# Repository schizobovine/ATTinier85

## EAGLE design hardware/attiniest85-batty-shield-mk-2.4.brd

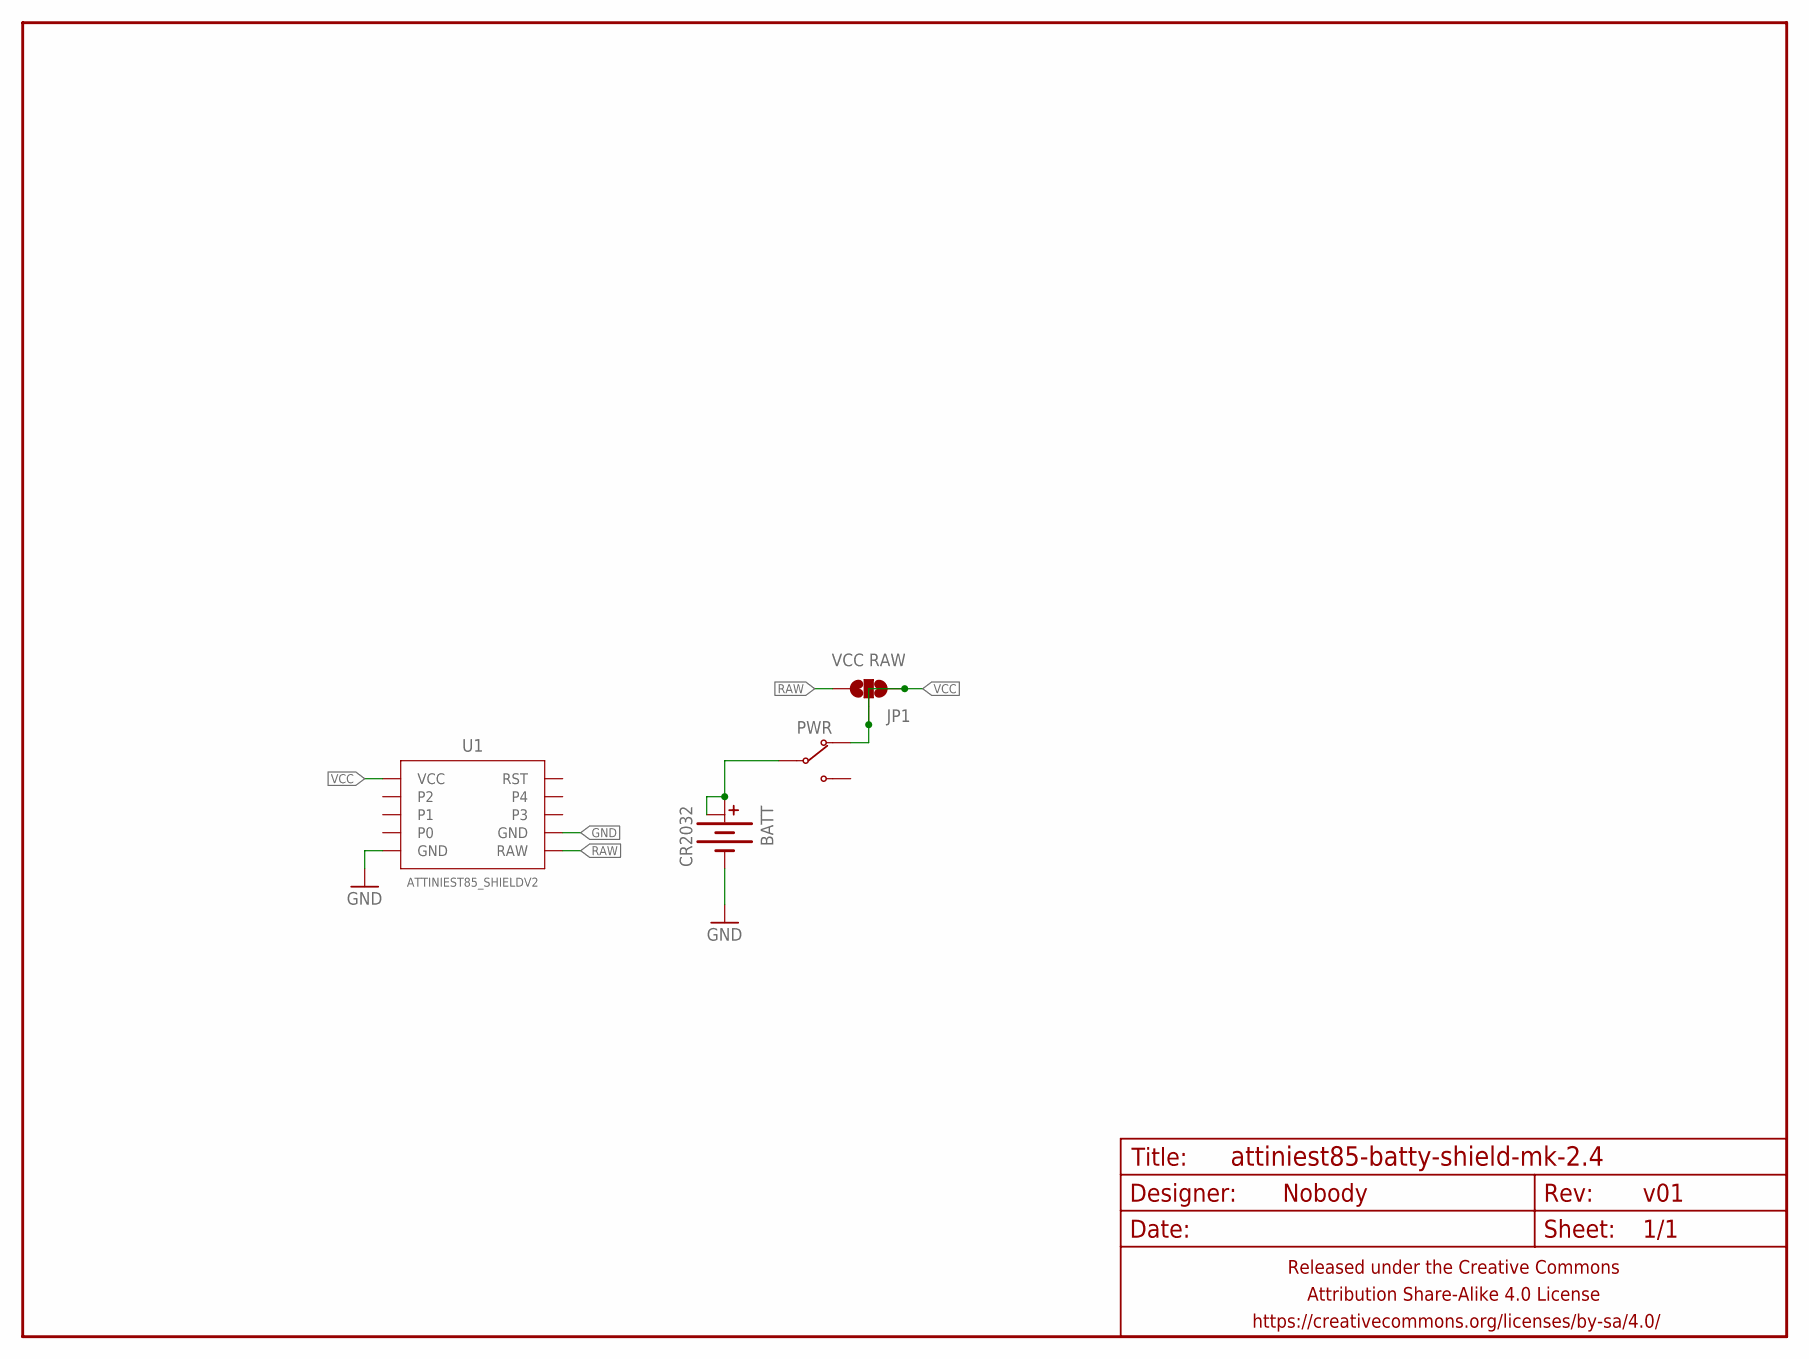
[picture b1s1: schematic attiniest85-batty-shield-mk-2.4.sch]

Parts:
BATT: CR2032; BATTCON_20MM_MINE
FRAME1: FRAME-LETTERNO_PACKAGE; DUMMY
JP1: VCC RAW; PAD-JUMPER-3-NO_YES_SILK_FULL_BOX
PWR: SWITCH-SPDTPTH-RA-2MM; SPDT-RA-2MM
U1: ATTINIEST85_SHIELDV2; ATTINIEST85_SHIELD_V2

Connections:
GND: BATT.BOTTOM (-), U1.GND@1 (GND), U1.GND@2 (GND)
RAW: JP1.1, U1.RAW
VBATT: BATT.TOP@1 (+), BATT.TOP@2 (+1), PWR.2 (COM)
VCC: JP1.2, JP1.3, PWR.1 (NC), U1.VCC

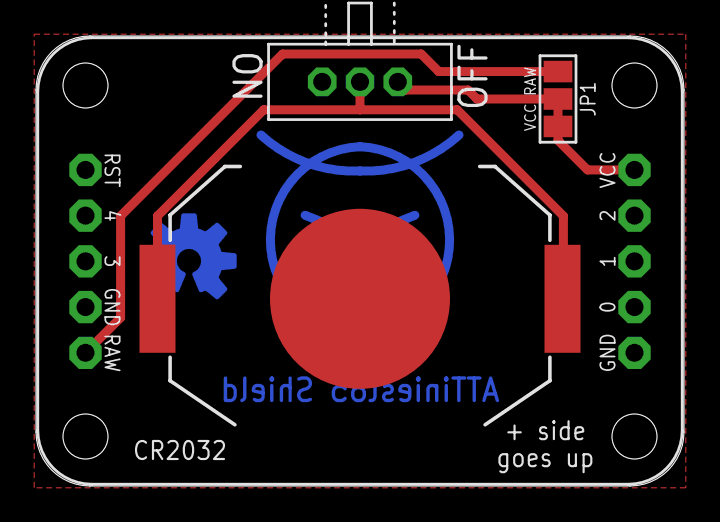
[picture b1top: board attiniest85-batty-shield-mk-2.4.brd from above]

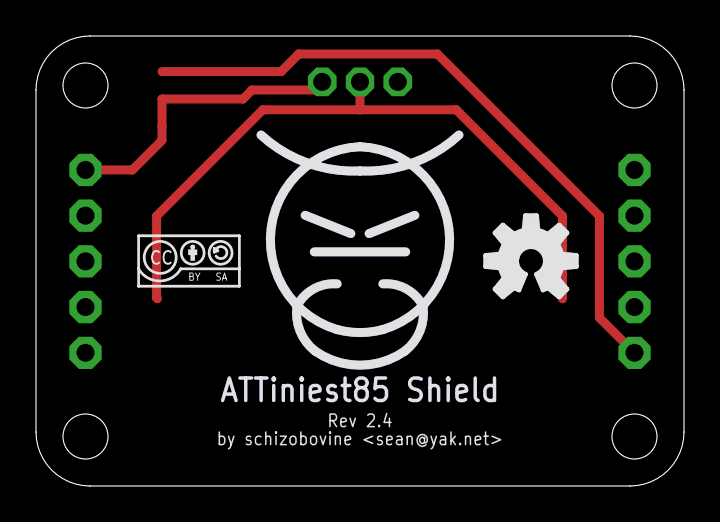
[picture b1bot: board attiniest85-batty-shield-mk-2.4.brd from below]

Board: 2 copper layers, 36.0 x 25.0 mm, 8 parts (3 on the bottom side), 4 nets.

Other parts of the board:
U$3: CC-BY-SA-4.0-NO-URL
U$4: OSHWLOGO_TOP_0.2
U$6: COW_METAL

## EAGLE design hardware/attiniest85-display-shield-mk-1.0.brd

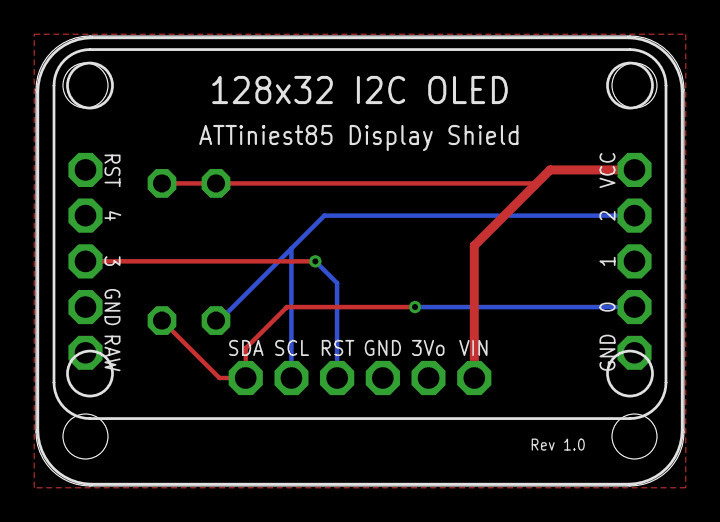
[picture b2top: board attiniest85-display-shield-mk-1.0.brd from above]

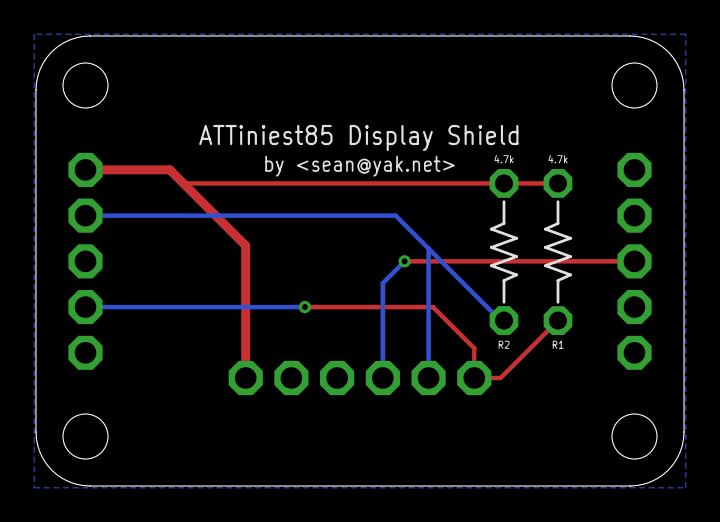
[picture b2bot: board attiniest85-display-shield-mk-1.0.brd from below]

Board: 2 copper layers, 36.0 x 25.0 mm, 5 parts (2 on the bottom side), 5 nets.

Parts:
DISPLAY1: Adafruit 128x32 OLED; ADAFRUIT_128X32_OLED_I2C_CLOSER_NOHOLES
FRAME1: DUMMY
R1, R2: 4.7k; RESISTOR-AXIAL-PTH-7.62MM
U1: ATTINIEST85_SHIELDV2; ATTINIEST85_SHIELD_V2

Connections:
DISP_RST: DISPLAY1.RST, U1.3
GND: DISPLAY1.GND, U1.GND@1, U1.GND@2
SCL: DISPLAY1.SCL, R2.P$1, U1.2
SDA: DISPLAY1.SDA, R1.P$1, U1.0
VCC: DISPLAY1.VIN, R1.P$2, R2.P$2, U1.VCC

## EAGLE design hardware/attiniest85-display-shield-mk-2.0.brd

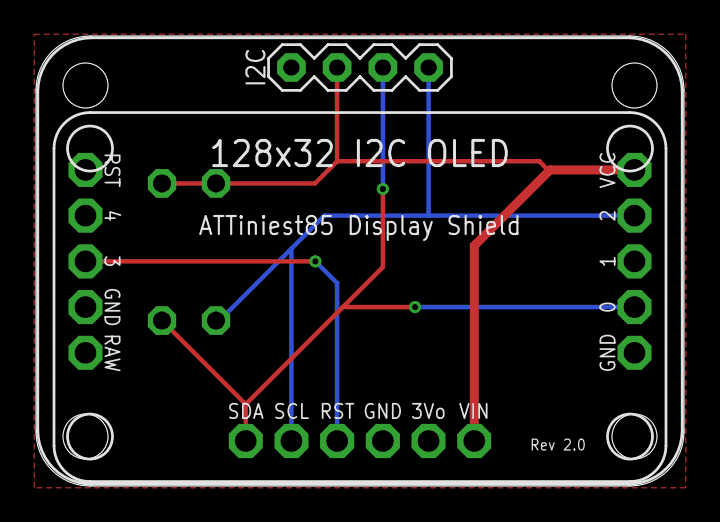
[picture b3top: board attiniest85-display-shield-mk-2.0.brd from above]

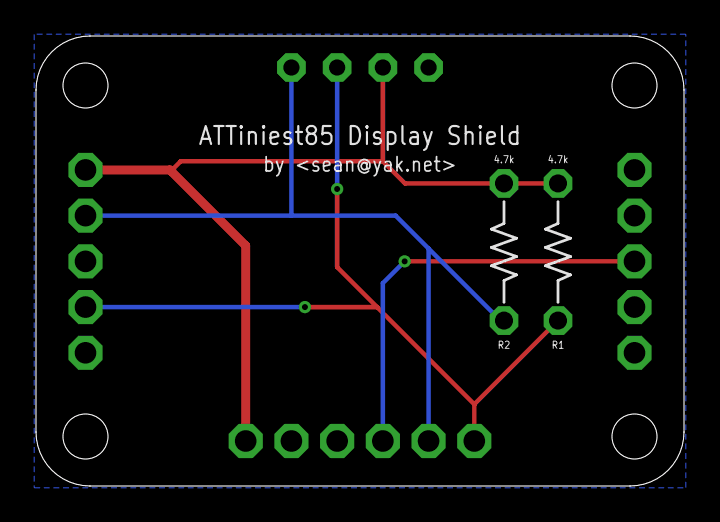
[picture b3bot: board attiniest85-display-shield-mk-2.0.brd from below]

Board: 2 copper layers, 36.0 x 25.0 mm, 6 parts (2 on the bottom side), 5 nets.

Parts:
DISPLAY1: Adafruit 128x32 OLED; ADAFRUIT_128X32_OLED_I2C_CLOSER_NOHOLES
FRAME1: DUMMY
I2C: M04PTH; 1X04-PTH-VERT
R1, R2: 4.7k; RESISTOR-AXIAL-PTH-7.62MM
U1: ATTINIEST85_SHIELDV2; ATTINIEST85_SHIELD_V2

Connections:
DISP_RST: DISPLAY1.RST, U1.3
GND: DISPLAY1.GND, I2C.1, U1.GND@1, U1.GND@2
SCL: DISPLAY1.SCL, I2C.4, R2.P$1, U1.2
SDA: DISPLAY1.SDA, I2C.3, R1.P$1, U1.0
VCC: DISPLAY1.VIN, I2C.2, R1.P$2, R2.P$2, U1.VCC

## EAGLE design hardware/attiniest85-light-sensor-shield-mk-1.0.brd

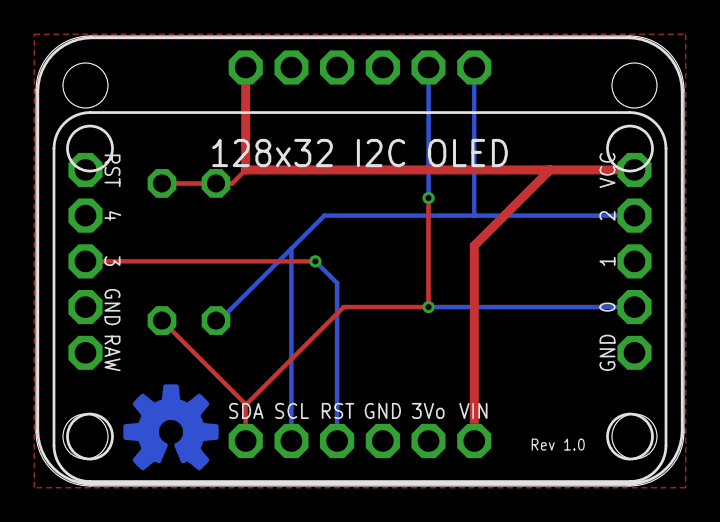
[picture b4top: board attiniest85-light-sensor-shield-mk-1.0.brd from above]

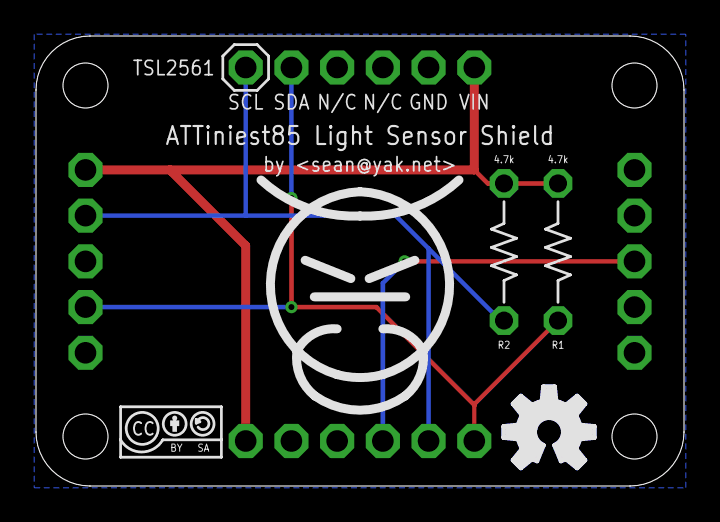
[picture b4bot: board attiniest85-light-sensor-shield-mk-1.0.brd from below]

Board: 2 copper layers, 36.0 x 25.0 mm, 9 parts (6 on the bottom side), 5 nets.

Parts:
DISPLAY1: Adafruit 128x32 OLED; ADAFRUIT_128X32_OLED_I2C_CLOSER_NOHOLES
FRAME1: DUMMY
R1, R2: 4.7k; RESISTOR-AXIAL-PTH-7.62MM
TSL2561: M06CLOSER; 1X06_CLOSER
U1: ATTINIEST85_SHIELDV2; ATTINIEST85_SHIELD_V2
U$1: COW
U$2: CC-BY-SA-4.0-NO-URL
U$3: OSHWLOGO_TOP_0.2

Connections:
DISP_RST: DISPLAY1.RST, U1.3
GND: DISPLAY1.GND, TSL2561.5, U1.GND@1, U1.GND@2
SCL: DISPLAY1.SCL, R2.P$1, TSL2561.1, U1.2
SDA: DISPLAY1.SDA, R1.P$1, TSL2561.2, U1.0
VCC: DISPLAY1.VIN, R1.P$2, R2.P$2, TSL2561.6, U1.VCC

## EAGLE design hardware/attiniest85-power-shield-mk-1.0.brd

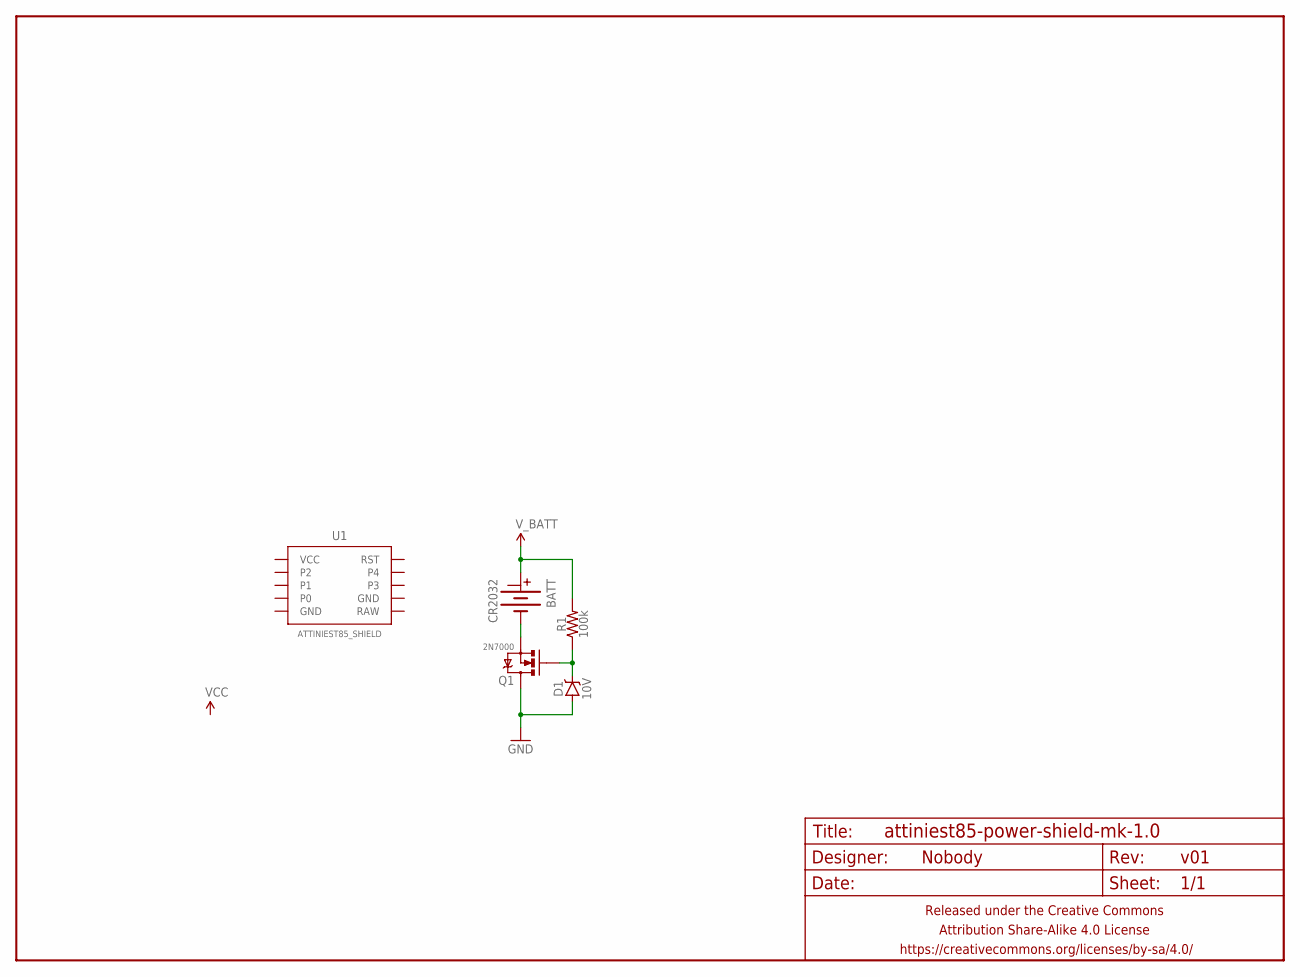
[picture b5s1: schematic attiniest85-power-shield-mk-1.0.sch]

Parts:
BATT: CR2032; BATTCON_20MM_MINE
D1: 10V; DIODE-ZENNER-7.62MM
FRAME1: FRAME-LETTERNO_PACKAGE; DUMMY
Q1: 2N7000; TO-92-AMMO
R1: 100k; RESISTOR-AXIAL-PTH-7.62MM
U1: ATTINIEST85_SHIELD

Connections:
GND: D1.A, Q1.3 (D)
unnamed: BATT.BOTTOM (-), Q1.1 (S)
unnamed: D1.K (C), Q1.2 (G), R1.P$1 (1)
V_BATT: BATT.TOP@1 (+), R1.P$2 (2)

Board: 2 copper layers, 6 parts (2 on the bottom side), 4 nets, no tracks yet.

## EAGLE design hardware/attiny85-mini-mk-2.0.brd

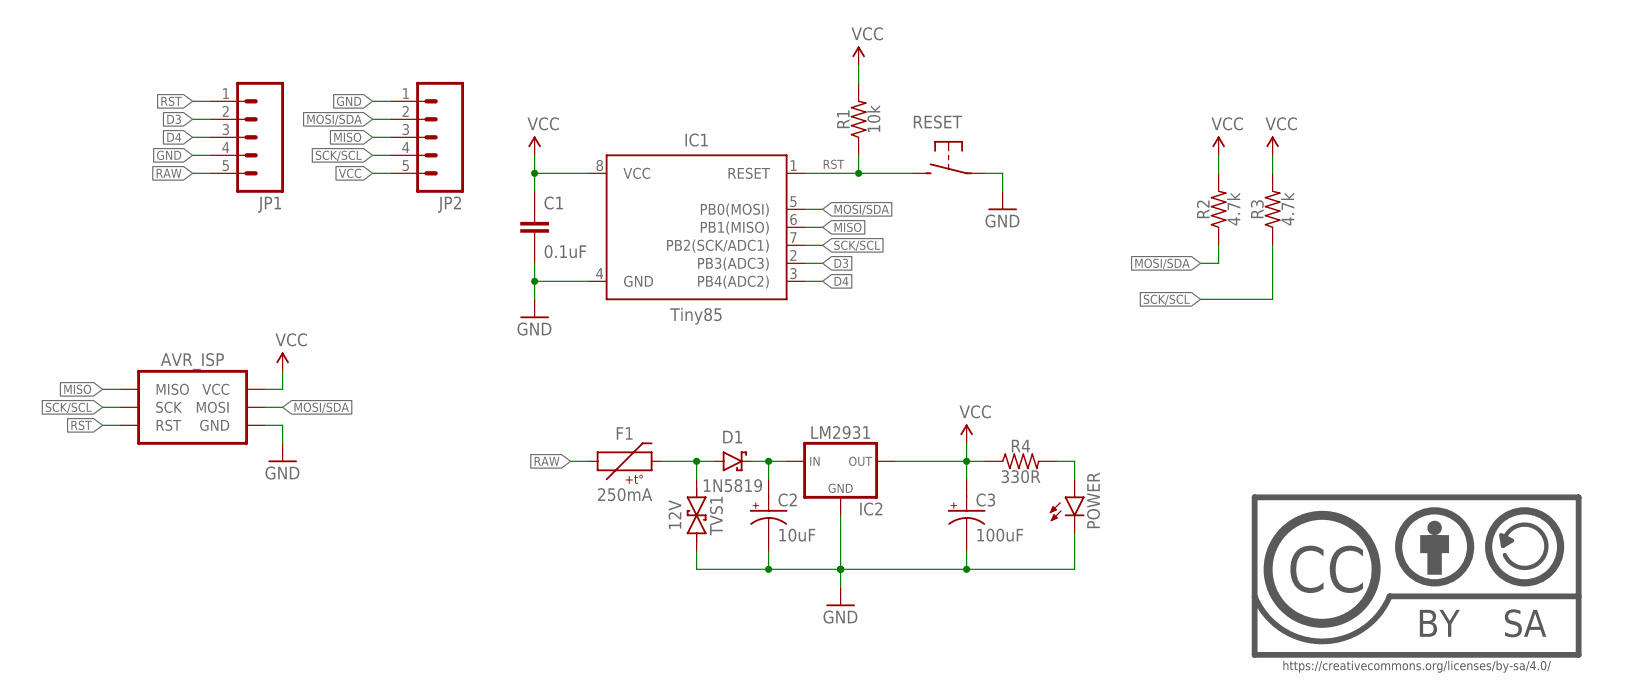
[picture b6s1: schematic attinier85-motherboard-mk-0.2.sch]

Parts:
AVR_ISP: AVR_SPI_PRG_6PTH; 2X3
C1: 0.1uF; C025-024X044
C2: 10uF; E2-5
C3: 100uF; E2,5-5
D1: 1N5819; DIODE-10.16MM
F1: 250mA; PTC-PTH-5.08MM
IC1: Tiny85; DIP08
IC2: LM2931; TO-92-AMMO
JP1, JP2: M05PTH; 1X05
POWER: LED3MM-LESS; LED3MM-LESSSILK
R1: 10k; RESISTOR-AXIAL-PTH-5.08MM
R2, R3: 4.7k; RESISTOR-AXIAL-PTH-5.08MM
R4: 330R; RESISTOR-AXIAL-PTH-5.08MM
RESET: DTS-6MM; DTS-3-SMALL-PADS
TVS1: 12V; DO-41-TVS
U$1: CC-BY-SA-4.0NO-URL; CC-BY-SA-4.0-NO-URL

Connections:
D3: IC1.2 (PB3(ADC3)), JP1.2
D4: IC1.3 (PB4(ADC2)), JP1.3
GND: AVR_ISP.6 (GND), C1.2, C2.-, C3.-, IC1.4 (GND), IC2.2 (GND), JP1.4, JP2.1, POWER.K (C), RESET.1, TVS1.P$2 (2)
MISO: AVR_ISP.1 (MISO), IC1.6 (PB1(MISO)), JP2.3
MOSI/SDA: AVR_ISP.4 (MOSI), IC1.5 (PB0(MOSI)), JP2.2, R2.P$1 (1)
unnamed: D1.A, F1.P$2 (2), TVS1.P$1 (1)
unnamed: C2.+, D1.C, IC2.1 (IN)
unnamed: POWER.A, R4.P$2 (2)
RAW: F1.P$1 (1), JP1.5
RST: AVR_ISP.5 (RST), IC1.1 (RESET), JP1.1, R1.P$1 (1), RESET.2
SCK/SCL: AVR_ISP.3 (SCK), IC1.7 (PB2(SCK/ADC1)), JP2.4, R3.P$1 (1)
VCC: AVR_ISP.2 (VCC), C1.1, C3.+, IC1.8 (VCC), IC2.3 (OUT), JP2.5, R1.P$2 (2), R2.P$2 (2), R3.P$2 (2), R4.P$1 (1)

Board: 2 copper layers, 19 parts (2 on the bottom side), 12 nets, no tracks yet.

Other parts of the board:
U$2: COW

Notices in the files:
parts and their libraries:
A_butts: creativecommons.org/licenses/by-sa/4.0
A_butts: https://creativecommons.org/licenses/by-sa/4.0
A_butts: Released under the Creative Commons Attribution Share-Alike 4.0 License
A_butts: Released under the Creative Commons
